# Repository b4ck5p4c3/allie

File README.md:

# Allie

## License & Attributions

Allie software is licensed under the GPL v3.0 (GNU General Public License, Version 3):

* Allie is based on [kormax/apple-home-key-reader](https://github.com/kormax/apple-home-key-reader) software under Apache License 2.0.

* It includes a modified version of [nfcpy](https://nfcpy.readthedocs.io/en/latest/) software under EUPL V.1.1.

* EMV core is highly influenced by [RfidResearchGroup/proxmark3](https://github.com/RfidResearchGroup/proxmark3) under GPL v3.0.

Hardware is licensed under CERN-OHL-S v2.0 (CERN Open Hardware Licence, Version 2 - Strongly Reciprocal).

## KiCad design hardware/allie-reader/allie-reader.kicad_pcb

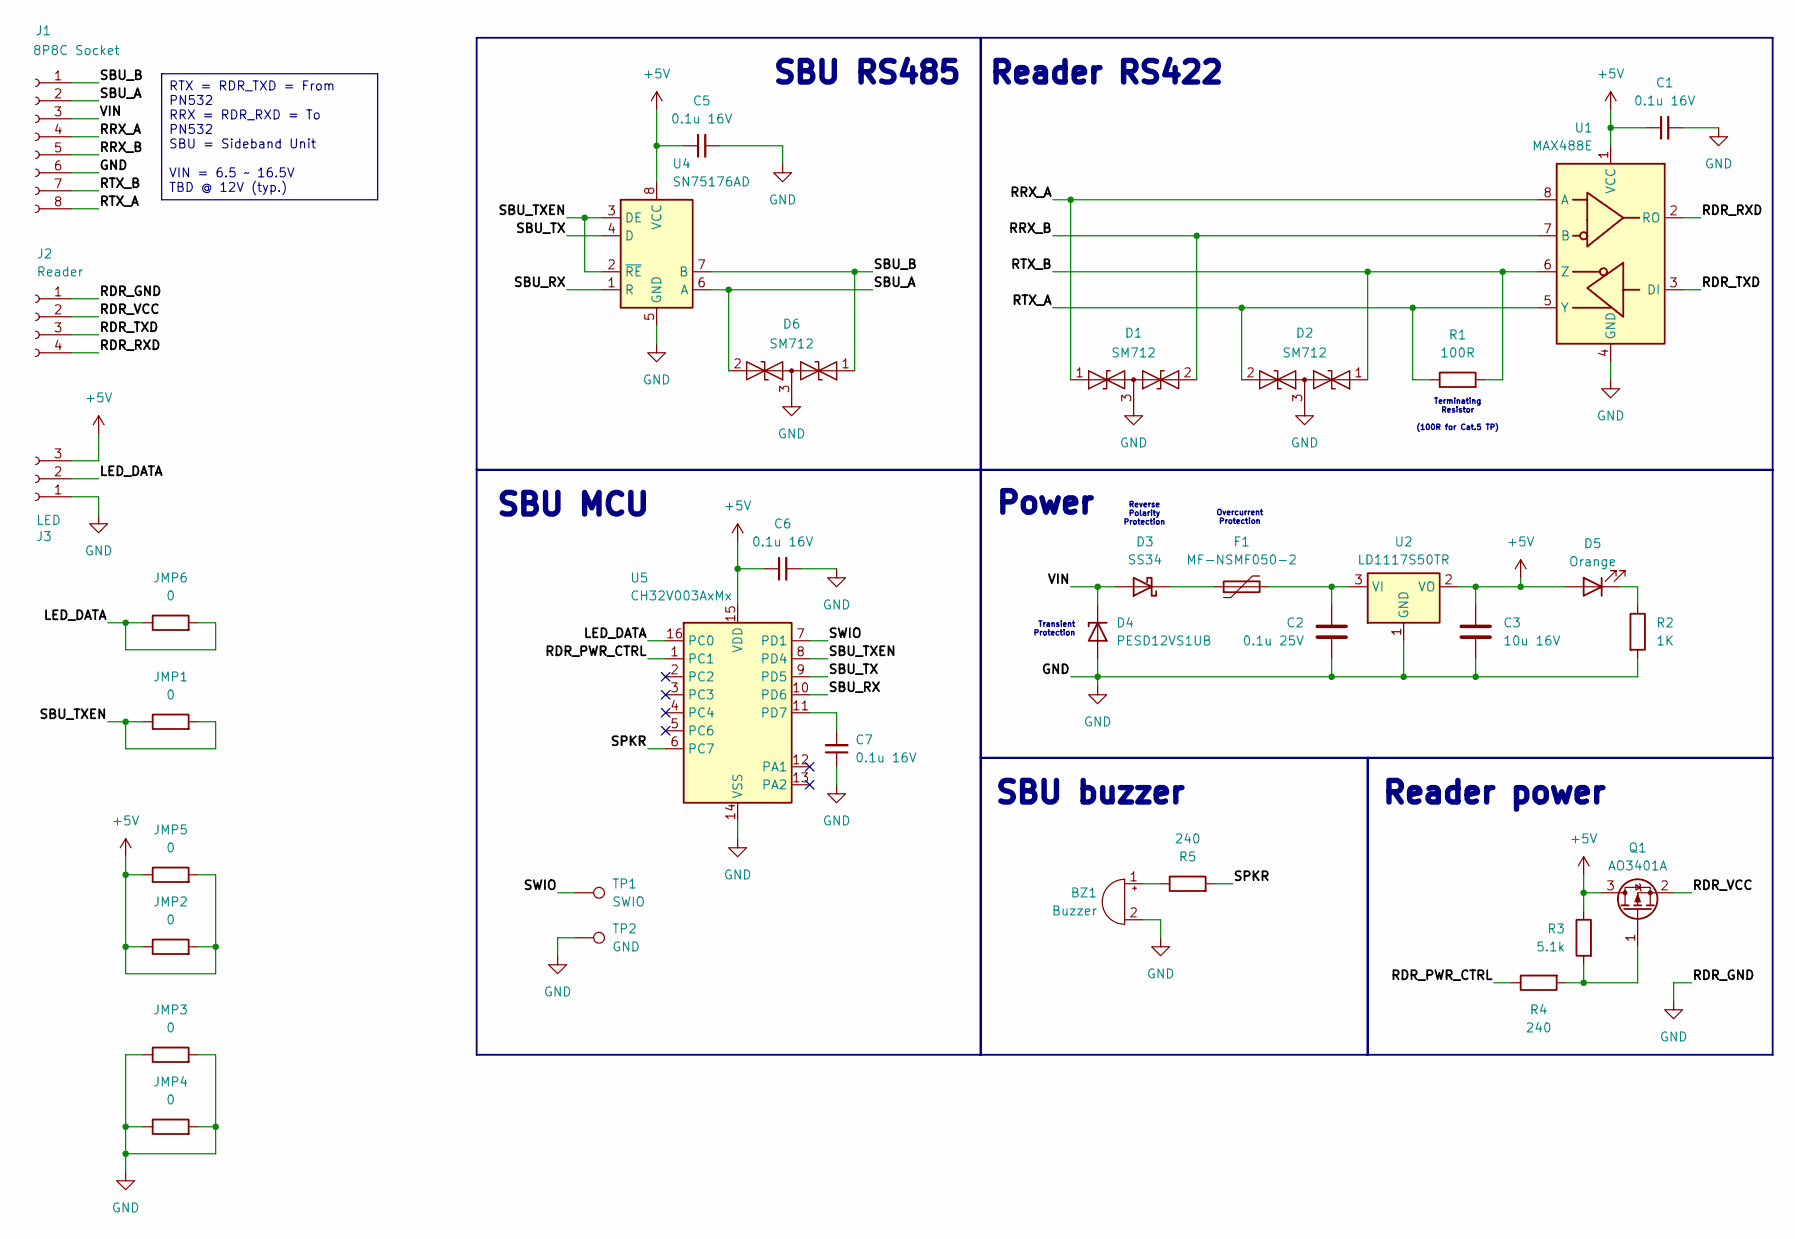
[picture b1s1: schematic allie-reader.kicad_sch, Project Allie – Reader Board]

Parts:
BZ1: Buzzer; Buzzer_17mm
C1, C5, C6, C7: 0.1u 16V; C_0805_2012Metric
C2: 0.1u 25V; C_0805_2012Metric
C3: 10u 16V; C_0805_2012Metric
D1, D2, D6: SM712; SOT-23
D3: SS34; D_SMA
D4: PESD12VS1UB; D_SOD-523
D5: Orange; LED_0805_2012Metric
F1: MF-NSMF050-2; Fuse_1206_3216Metric
J1: 8P8C Socket; JST_XH_B8B-XH-A_1x08_P2.50mm_Vertical
J2: Reader; PinSocket_1x04_P2.54mm_Vertical
J3: LED; JST_XH_B3B-XH-A_1x03_P2.50mm_Vertical
JMP1, JMP2, JMP3, JMP4, JMP5, JMP6: 0; R_1206_3216Metric
Q1: AO3401A; SOT-23
R1: 100R; R_1206_3216Metric
R2: 1K; R_0805_2012Metric
R3: 5.1k; R_0805_2012Metric
R4, R5: 240; R_0805_2012Metric
TP1: SWIO; TestPoint_Pad_D2.0mm
TP2: GND; TestPoint_Pad_D2.0mm
U1: MAX488E; SOIC-8_3.9x4.9mm_P1.27mm
U2: LD1117S50TR; SOT-223-3_TabPin2
U4: SN75176AD; SOIC-8_3.9x4.9mm_P1.27mm
U5: CH32V003AxMx; SOP-16_3.9x9.9mm_P1.27mm

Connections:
+5V: C1.1, C3.1, C5.1, C6.1, D5.2 (A), J3.3, JMP2.1, JMP2.2, JMP5.1, JMP5.2, Q1.3 (D), R3.1, U1.1 (VCC), U2.2 (VO), U4.8 (VCC), U5.15 (VDD)
/LED_DATA: J3.2, JMP6.1, JMP6.2, U5.16 (PC0)
/RDR_PWR_CTRL: R4.1, U5.1 (PC1)
/RDR_RXD: J2.4, U1.2 (RO)
/RDR_TXD: J2.3, U1.3 (DI)
/RDR_VCC: J2.2, Q1.2 (S)
/RRX_A: D1.1 (A1), J1.4, U1.8 (A)
/RRX_B: D1.2 (A2), J1.5, U1.7 (B)
/RTX_A: D2.2 (A2), J1.8, R1.1, U1.5 (Y)
/RTX_B: D2.1 (A1), J1.7, R1.2, U1.6 (Z)
/SBU_A: D6.2 (A2), J1.2, U4.6 (A)
/SBU_B: D6.1 (A1), J1.1, U4.7 (B)
/SBU_RX: U4.1 (R), U5.10 (PD6)
/SBU_TX: U4.4 (D), U5.9 (PD5)
/SBU_TXEN: JMP1.1, JMP1.2, U4.2 (~RE), U4.3 (DE), U5.8 (PD4)
/SPKR: R5.2, U5.6 (PC7)
/SWIO: TP1.1, U5.7 (PD1)
/VIN: D3.2 (A), D4.1 (K), J1.3
GND: BZ1.2 (-), C1.2, C2.2, C3.2, C5.2, C6.2, C7.1, D1.3 (common), D2.3 (common), D4.2 (A), D6.3 (common), J1.6, J2.1, J3.1, JMP3.1, JMP3.2, JMP4.1, JMP4.2, R2.2, TP2.1, U1.4 (GND), U2.1 (GND), U4.5 (GND), U5.14 (VSS)
unnamed: BZ1.1 (+), R5.1
unnamed: D3.1 (K), F1.1
unnamed: D5.1 (K), R2.1
unnamed: Q1.1 (G), R3.2, R4.2
unnamed: C2.1, F1.2, U2.3 (VI)
unnamed: C7.2, U5.11 (PD7)

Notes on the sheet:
SBU MCU
SBU RS485
Reverse Polarity Protection
Power
Terminating Resistor (100R for Cat.5 TP)
SBU buzzer
Reader power
Overcurrent Protection
Reader RS422
Transient Protection
RTX = RDR_TXD = From PN532 RRX = RDR_RXD = To PN532 SBU = Sideband Unit VIN = 6.5 ~ 16.5V TBD @ 12V (typ.)

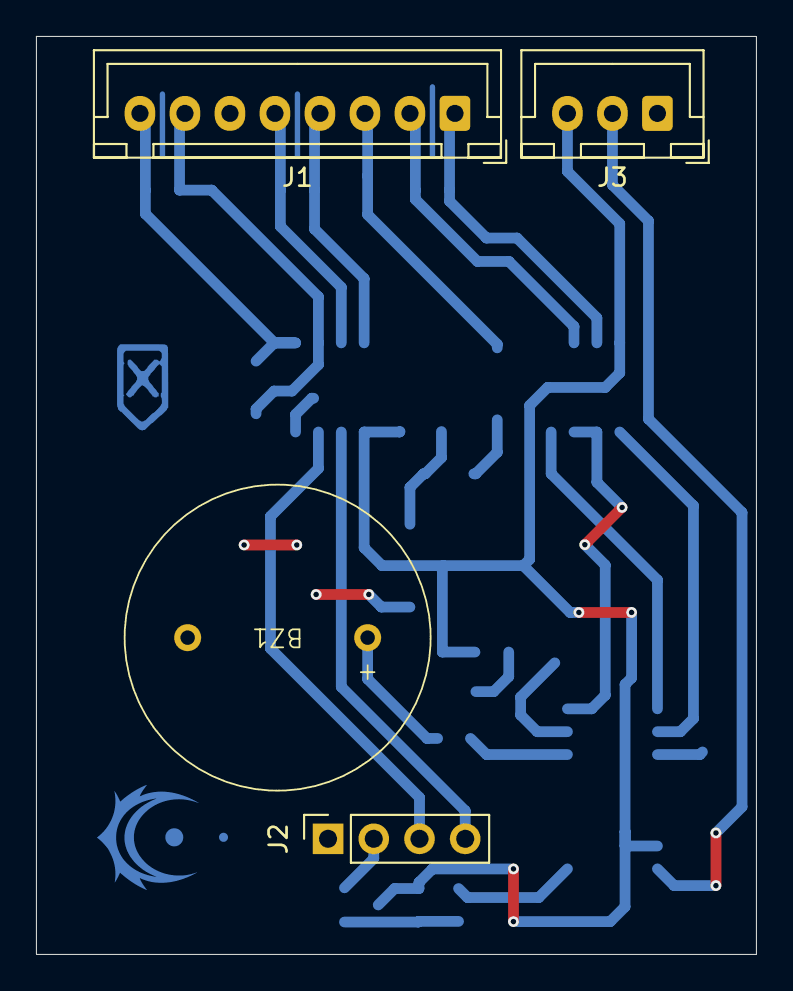
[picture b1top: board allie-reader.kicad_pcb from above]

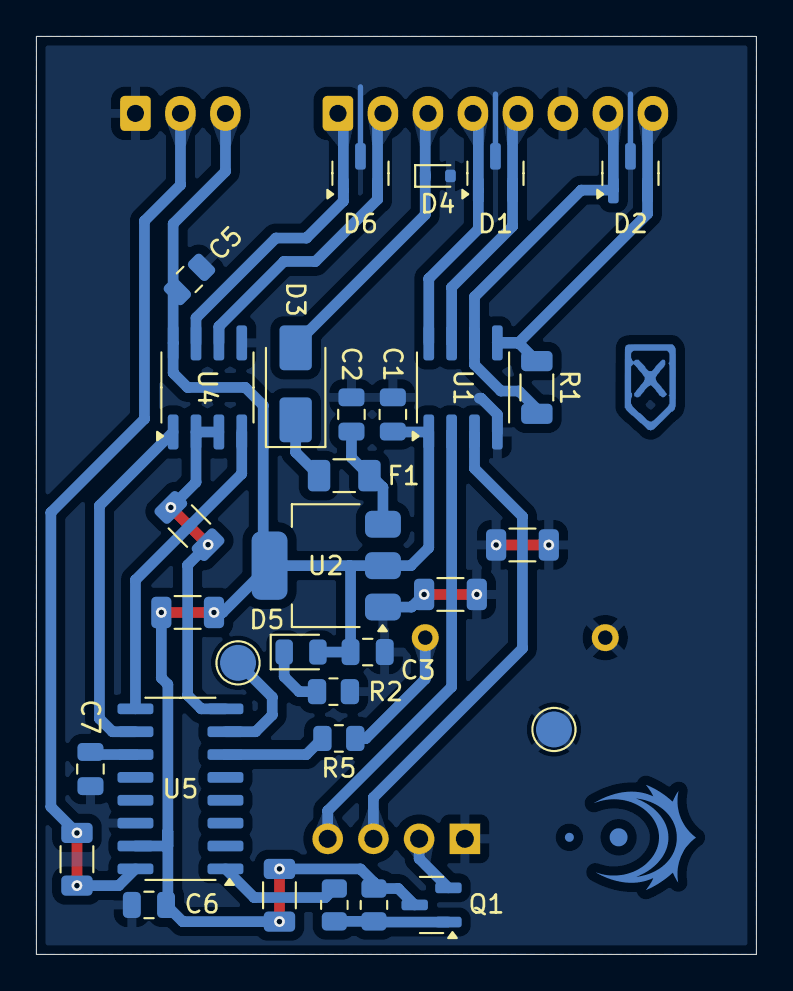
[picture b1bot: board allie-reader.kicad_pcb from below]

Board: 2 copper layers, 40.0 x 51.0 mm, 35 parts (31 on the bottom side), 25 nets.

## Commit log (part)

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2026-01-10 feat(hw/reader): schematic draft
2026-01-10 add: pcb for allie
2026-01-10 fix: add drops to pcb
